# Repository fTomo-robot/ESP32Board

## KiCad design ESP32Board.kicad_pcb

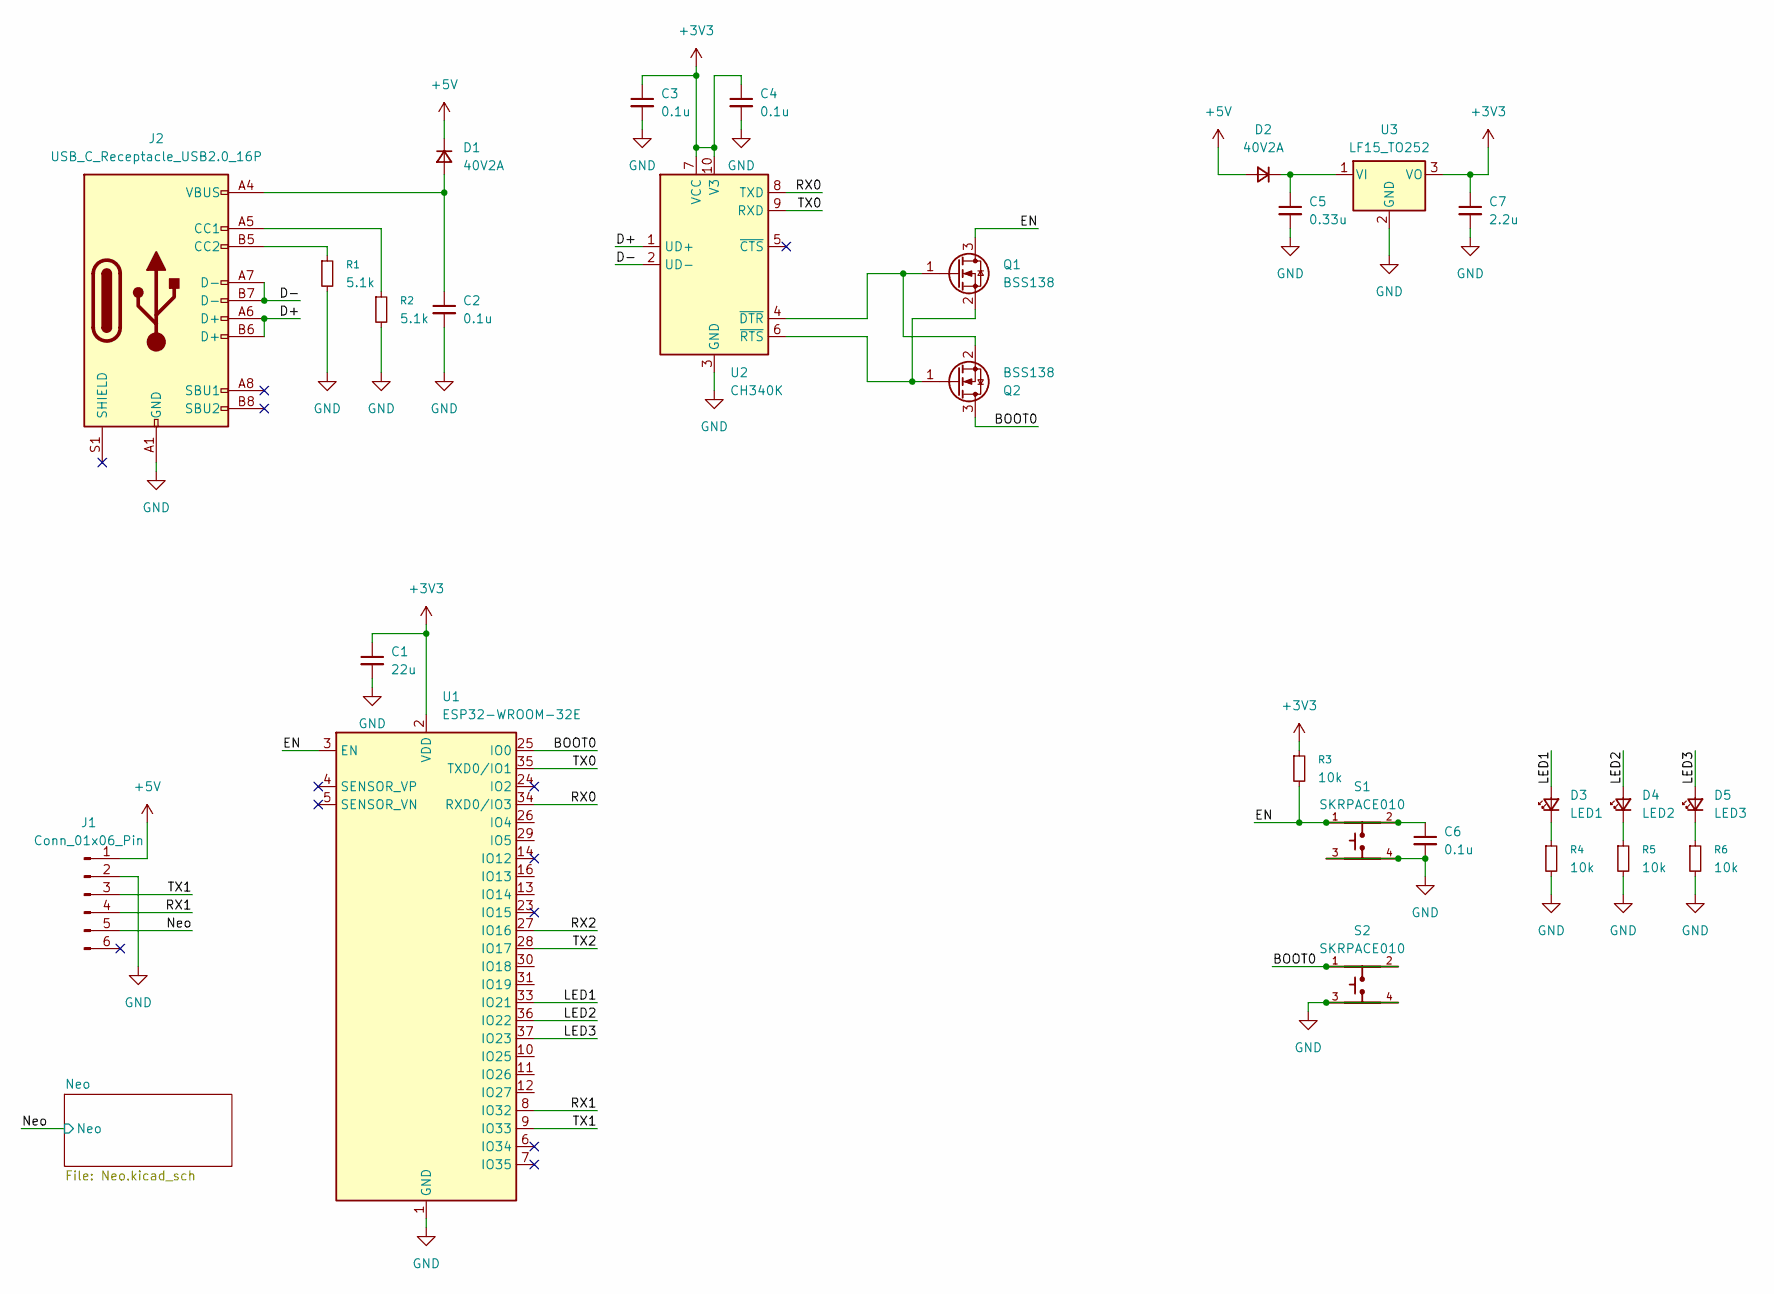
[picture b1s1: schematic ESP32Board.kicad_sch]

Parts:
C1: 22u; C_0805_2012Metric
C2, C3, C4, C6: 0.1u; C_0603_1608Metric
C5: 0.33u; C_0603_1608Metric
C7: 2.2u; C_0805_2012Metric
D1, D2: 40V2A; D_SOD-123F
D3: LED1; LED_0603_1608Metric
D4: LED2; LED_0603_1608Metric
D5: LED3; LED_0603_1608Metric
J1: Conn_01x06_Pin; PinSocket_2x03_P2.54mm_Vertical
J2: USB_C_Receptacle_USB2.0_16P; USB_C_Receptacle_HCTL_HC-TYPE-C-16P-01A
Q1, Q2: BSS138; SOT-23
R1, R2: 5.1k; R_0603_1608Metric
R3, R4, R5, R6: 10k; R_0603_1608Metric
S1, S2: SKRPACE010; SW_SKRPACE010
U1: ESP32-WROOM-32E; ESP32-WROOM-32D
U2: CH340K; SSOP-10-1EP_3.9x4.9mm_P1mm_EP2.1x3.3mm
U3: LF15_TO252; TO-252-2

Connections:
+3V3: C1.1, C3.1, C4.1, C7.1, R3.1, U1.2 (VDD), U2.7 (VCC), U2.10 (V3), U3.3 (VO)
+5V: D1.1 (K), D2.2 (A), J1.1; also elsewhere on the board
/BOOT0: Q2.3 (D), S2.1, S2.2, U1.25 (IO0)
/D+: J2.A6 (D+), J2.B6 (D+), U2.1 (UD+)
/D-: J2.A7 (D-), J2.B7 (D-), U2.2 (UD-)
/EN: C6.1, Q1.3 (D), R3.2, S1.1, S1.2, U1.3 (EN)
/LED1: D3.2 (A), U1.33 (IO21)
/LED2: D4.2 (A), U1.36 (IO22)
/LED3: D5.2 (A), U1.37 (IO23)
/Neo: J1.5; also elsewhere on the board
/RX0: U1.34 (RXD0/IO3), U2.8 (TXD)
/RX1: J1.4, U1.8 (IO32)
/RX2: U1.27 (IO16)
/TX0: U1.35 (TXD0/IO1), U2.9 (RXD)
/TX1: J1.3, U1.9 (IO33)
/TX2: U1.28 (IO17)
GND: C1.2, C2.2, C3.2, C4.2, C5.2, C6.2, C7.2, J1.2, J2.A1 (GND), J2.A12 (GND), J2.B1 (GND), J2.B12 (GND), R1.2, R2.2, R4.2, R5.2, R6.2, S1.3, S1.4, S2.3, S2.4, U1.1 (GND), U1.15 (GND), U1.38 (GND), U1.39 (GND), U2.3 (GND), U2.11 (GND), U3.2 (GND); also elsewhere on the board
unnamed: C2.1, D1.2 (A), J2.A4 (VBUS), J2.A9 (VBUS), J2.B4 (VBUS), J2.B9 (VBUS)
unnamed: C5.1, D2.1 (K), U3.1 (VI)
unnamed: D3.1 (K), R4.1
unnamed: D4.1 (K), R5.1
unnamed: D5.1 (K), R6.1
unnamed: J2.A5 (CC1), R2.1
unnamed: J2.B5 (CC2), R1.1
unnamed: Q1.1 (G), Q2.2 (S), U2.4 (~DTR)
unnamed: Q1.2 (S), Q2.1 (G), U2.6 (~RTS)

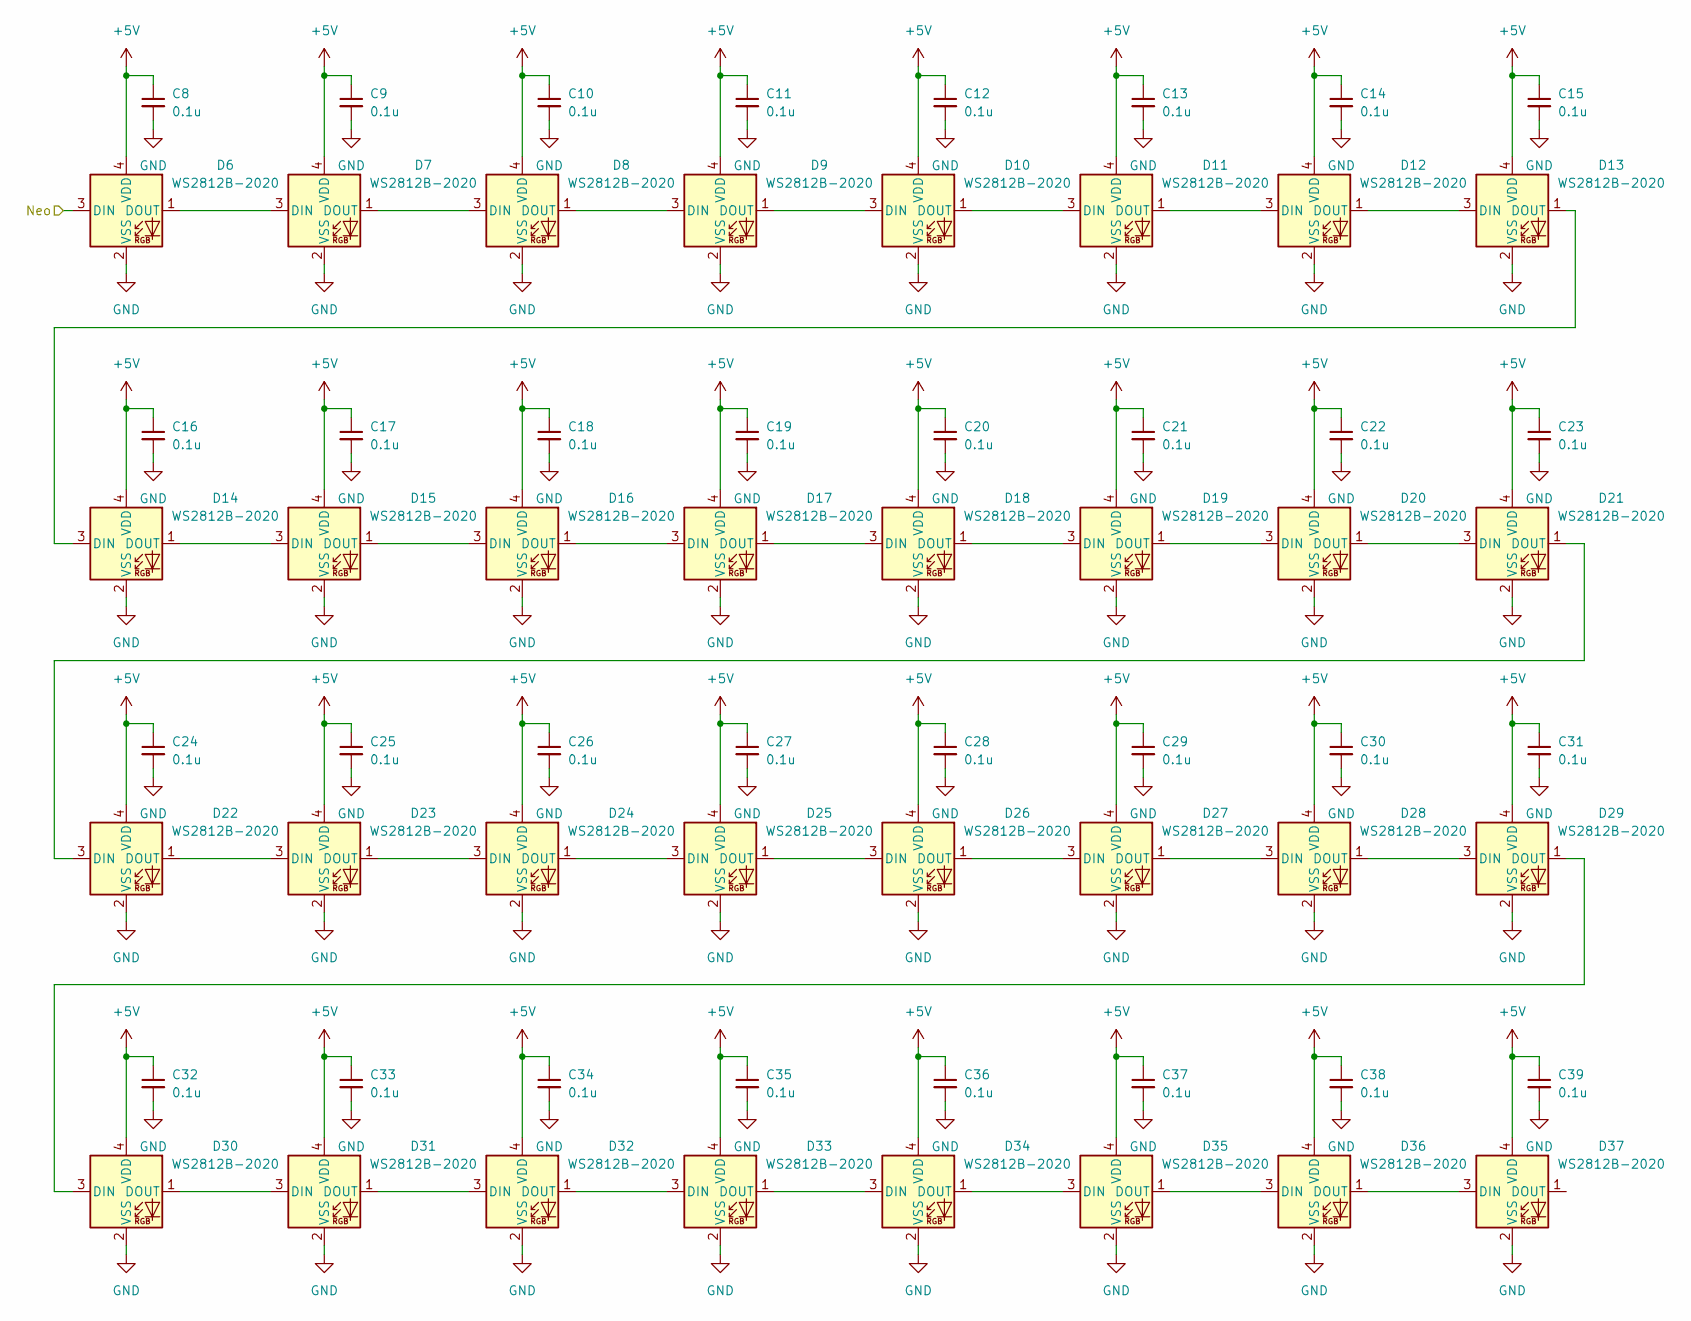
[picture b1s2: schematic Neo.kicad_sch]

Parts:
C8, C9, C10, C11, C12, C13, C14, C15, C16, C17, C18, C19, C20, C21, C22, C23, C24, C25, C26, C27, C28, C29, C30, C31, C32, C33, C34, C35, C36, C37, C38, C39: 0.1u; C_0402_1005Metric
D6, D7, D8, D9, D10, D11, D12, D13, D14, D15, D16, D17, D18, D19, D20, D21, D22, D23, D24, D25, D26, D27, D28, D29, D30, D31, D32, D33, D34, D35, D36, D37: WS2812B-2020; LED_WS2812B-2020_PLCC4_2.0x2.0mm

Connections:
+5V: C8.1, C9.1, C10.1, C11.1, C12.1, C13.1, C14.1, C15.1, C16.1, C17.1, C18.1, C19.1, C20.1, C21.1, C22.1, C23.1, C24.1, C25.1, C26.1, C27.1, C28.1, C29.1, C30.1, C31.1, C32.1, C33.1, C34.1, C35.1, C36.1, C37.1, C38.1, C39.1, D6.4 (VDD), D7.4 (VDD), D8.4 (VDD), D9.4 (VDD), D10.4 (VDD), D11.4 (VDD), D12.4 (VDD), D13.4 (VDD), D14.4 (VDD), D15.4 (VDD), D16.4 (VDD), D17.4 (VDD), D18.4 (VDD), D19.4 (VDD), D20.4 (VDD), D21.4 (VDD), D22.4 (VDD), D23.4 (VDD), D24.4 (VDD), D25.4 (VDD), D26.4 (VDD), D27.4 (VDD), D28.4 (VDD), D29.4 (VDD), D30.4 (VDD), D31.4 (VDD), D32.4 (VDD), D33.4 (VDD), D34.4 (VDD), D35.4 (VDD), D36.4 (VDD), D37.4 (VDD); also elsewhere on the board
/Neo: D6.3 (DIN); also elsewhere on the board
GND: C8.2, C9.2, C10.2, C11.2, C12.2, C13.2, C14.2, C15.2, C16.2, C17.2, C18.2, C19.2, C20.2, C21.2, C22.2, C23.2, C24.2, C25.2, C26.2, C27.2, C28.2, C29.2, C30.2, C31.2, C32.2, C33.2, C34.2, C35.2, C36.2, C37.2, C38.2, C39.2, D6.2 (VSS), D7.2 (VSS), D8.2 (VSS), D9.2 (VSS), D10.2 (VSS), D11.2 (VSS), D12.2 (VSS), D13.2 (VSS), D14.2 (VSS), D15.2 (VSS), D16.2 (VSS), D17.2 (VSS), D18.2 (VSS), D19.2 (VSS), D20.2 (VSS), D21.2 (VSS), D22.2 (VSS), D23.2 (VSS), D24.2 (VSS), D25.2 (VSS), D26.2 (VSS), D27.2 (VSS), D28.2 (VSS), D29.2 (VSS), D30.2 (VSS), D31.2 (VSS), D32.2 (VSS), D33.2 (VSS), D34.2 (VSS), D35.2 (VSS), D36.2 (VSS), D37.2 (VSS); also elsewhere on the board
unnamed: D6.1 (DOUT), D7.3 (DIN)
unnamed: D7.1 (DOUT), D8.3 (DIN)
unnamed: D8.1 (DOUT), D9.3 (DIN)
unnamed: D9.1 (DOUT), D10.3 (DIN)
unnamed: D10.1 (DOUT), D11.3 (DIN)
unnamed: D11.1 (DOUT), D12.3 (DIN)
unnamed: D12.1 (DOUT), D13.3 (DIN)
unnamed: D13.1 (DOUT), D14.3 (DIN)
unnamed: D14.1 (DOUT), D15.3 (DIN)
unnamed: D15.1 (DOUT), D16.3 (DIN)
unnamed: D16.1 (DOUT), D17.3 (DIN)
unnamed: D17.1 (DOUT), D18.3 (DIN)
unnamed: D18.1 (DOUT), D19.3 (DIN)
unnamed: D19.1 (DOUT), D20.3 (DIN)
unnamed: D20.1 (DOUT), D21.3 (DIN)
unnamed: D21.1 (DOUT), D22.3 (DIN)
unnamed: D22.1 (DOUT), D23.3 (DIN)
unnamed: D23.1 (DOUT), D24.3 (DIN)
unnamed: D24.1 (DOUT), D25.3 (DIN)
unnamed: D25.1 (DOUT), D26.3 (DIN)
unnamed: D26.1 (DOUT), D27.3 (DIN)
unnamed: D27.1 (DOUT), D28.3 (DIN)
unnamed: D28.1 (DOUT), D29.3 (DIN)
unnamed: D29.1 (DOUT), D30.3 (DIN)
unnamed: D30.1 (DOUT), D31.3 (DIN)
unnamed: D31.1 (DOUT), D32.3 (DIN)
unnamed: D32.1 (DOUT), D33.3 (DIN)
unnamed: D33.1 (DOUT), D34.3 (DIN)
unnamed: D34.1 (DOUT), D35.3 (DIN)
unnamed: D35.1 (DOUT), D36.3 (DIN)
unnamed: D36.1 (DOUT), D37.3 (DIN)

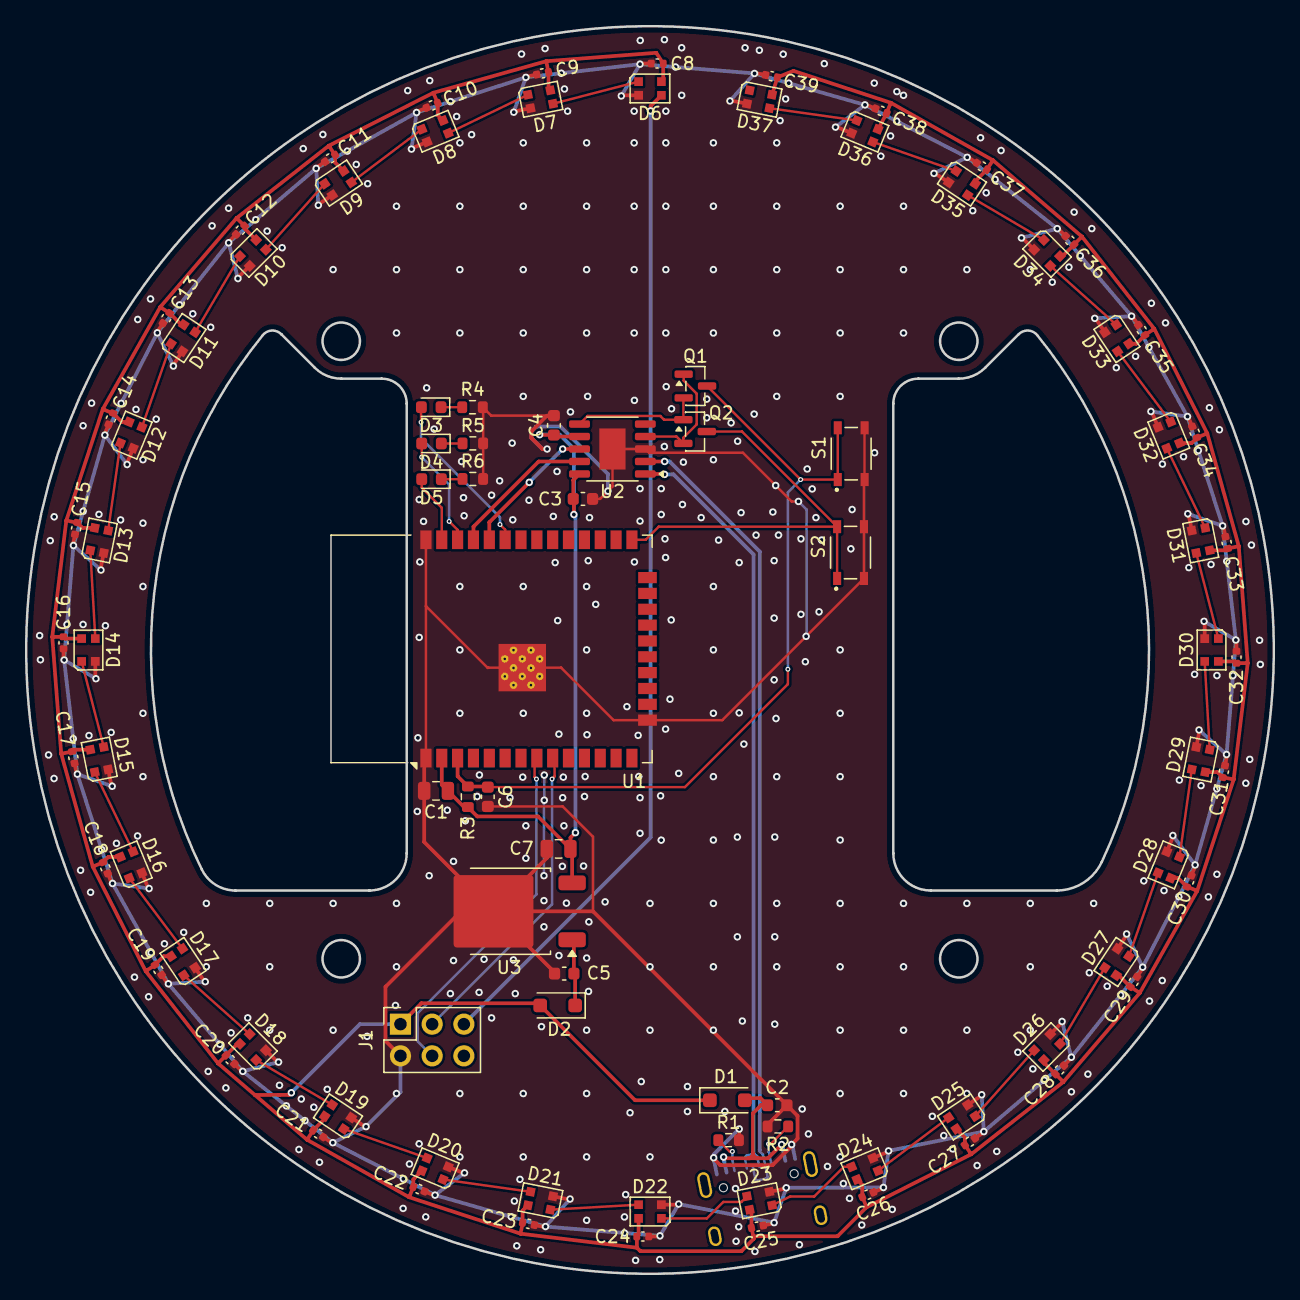
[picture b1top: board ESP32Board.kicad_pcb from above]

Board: 2 copper layers, 100.0 x 100.0 mm, 91 parts (1 on the bottom side), 55 nets.

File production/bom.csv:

Designator,Footprint,Quantity,Value,LCSC Part #
C1,0805,1,22u,
"C10, C11, C12, C13, C14, C15, C16, C17, C18, C19, C20, C21, C22, C23, C24, C25, C26, C27, C28, C29, C30, C31, C32, C33, C34, C35, C36, C37, C38, C39, C8, C9",0402,32,0.1u,
"C2, C3, C4, C6",0603,4,0.1u,
C5,0603,1,0.33u,
C7,0805,1,2.2u,
"D1, D2",D_SOD-123F,2,40V2A,
"D10, D11, D12, D13, D14, D15, D16, D17, D18, D19, D20, D21, D22, D23, D24, D25, D26, D27, D28, D29, D30, D31, D32, D33, D34, D35, D36, D37, D6, D7, D8, D9",LED_WS2812B-2020_PLCC4_2.0x2.0mm,32,WS2812B-2020,
D3,0603,1,LED1,
D4,0603,1,LED2,
D5,0603,1,LED3,
J1,PinSocket_2x03_P2.54mm_Vertical,1,Conn_01x06_Pin,
J2,USB_C_Receptacle_HCTL_HC-TYPE-C-16P-01A,1,USB_C_Receptacle_USB2.0_16P,
"Q1, Q2",SOT-23,2,BSS138,
"R1, R2",0603,2,5.1k,
"R3, R4, R5, R6",0603,4,10k,
"S1, S2",SW_SKRPACE010,2,SKRPACE010,
U1,ESP32-WROOM-32D,1,ESP32-WROOM-32E,
U2,SSOP-10-1EP_3.9x4.9mm_P1mm_EP2.1x3.3mm,1,CH340K,
U3,TO-252-2,1,LF15_TO252,

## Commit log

2026-04-10 アップロード
2026-04-10 ビア打ち
2026-04-10 シルク調整
2026-04-10 ビアうち
2026-04-23 なんか編集した
